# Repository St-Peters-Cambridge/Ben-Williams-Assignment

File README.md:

NSN: 144724831
Name: Ben Williams
Project: Ground control station for model rockets

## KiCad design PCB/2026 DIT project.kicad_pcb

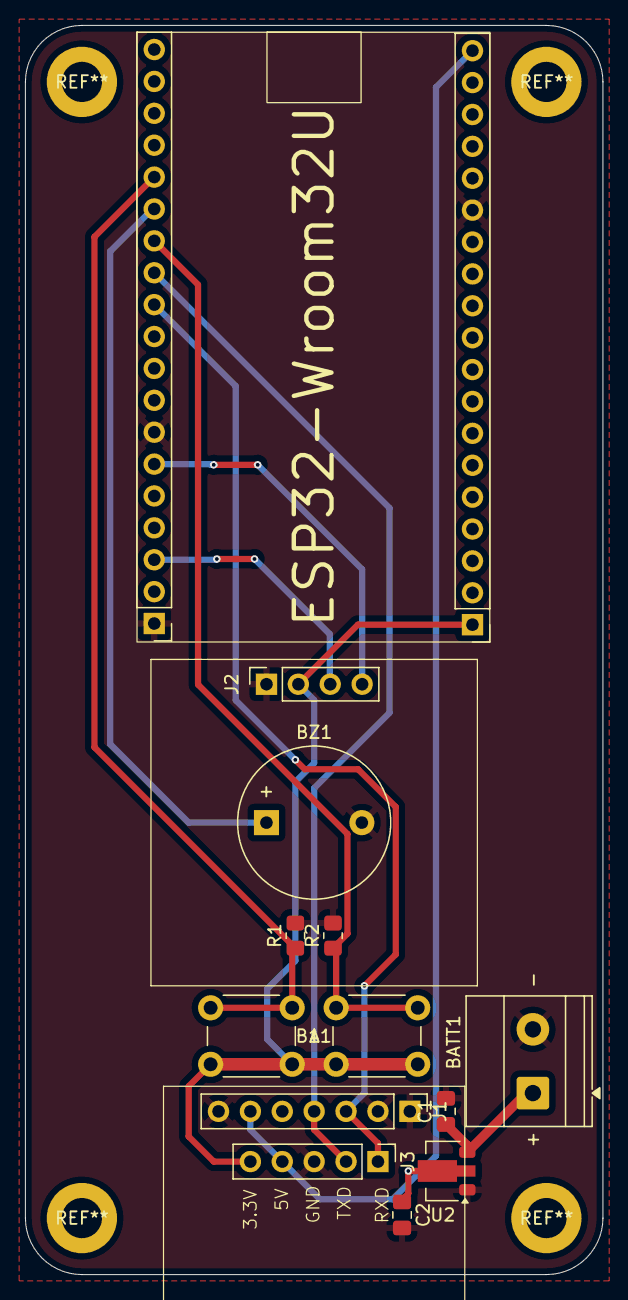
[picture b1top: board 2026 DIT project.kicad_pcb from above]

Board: 2 copper layers, 46.0 x 99.5 mm, 13 parts (0 on the bottom side), 11 nets.

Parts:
A1: SW_Push_Open_Dual; SW_PUSH_6mm
B1: SW_Push_Open_Dual; SW_PUSH_6mm
BATT1: Screw_Terminal_01x02; TerminalBlock_Phoenix_MKDS-1,5-2-5.08_1x02_P5.08mm_Horizont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
BZ1: Buzzer; Buzzer_12x9.5RM7.6
C1: 10u; C_0805_2012Metric_Pad1.18x1.45mm_HandSolder
C2: 22u; C_0805_2012Metric_Pad1.18x1.45mm_HandSolder
J1: Conn_01x07_Socket; PinHeader_1x07_P2.54mm_Vertical
J2: Conn_01x04_Socket; PinSocket_1x04_P2.54mm_Vertical
J3: Conn_01x05_Pin; PinHeader_1x05_P2.54mm_Vertical
R1, R2: 10k; R_0805_2012Metric_Pad1.20x1.40mm_HandSolder
U1: ESP32-WROOM32U; Board
U2: AMS1117-5.0; SOT-89-3

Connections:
+3V3: A1.1, B1.1, J2.2, J3.5, U1.3V3
+5V: C2.1, J1.6, J3.4, U1.5V, U2.2 (VO)
/BTN_A: A1.2, R1.1, U1.2
/BTN_B: B1.2, R2.1, U1.4
/Buzzer: BZ1.1 (+), U1.0
/RXD: J1.3, J3.1, U1.17
/SCL: J2.3, U1.22
/SDA: J2.4, U1.21
/TXD: J1.4, J3.2, U1.16
GND: BATT1.2, BZ1.2 (-), C1.2, C2.2, J1.1, J1.2, J1.7, J2.1, J3.3, R1.2, R2.2, U1.GND, U2.1 (GND)
VCC: BATT1.1, C1.1, U2.3 (VI)

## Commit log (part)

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2026-03-30 Basic setup of app
    Adding all files and basic setup
2026-03-30 Added all menus for PC
2026-03-30 Fixed Linking
2026-03-30 Add README
2026-03-30 Fixing for Pages
2026-03-30 Remove Folder
2026-03-31 Adding Circuit designs
2026-04-21 Work on home page
    Work for 21/04/2026 period 5
2026-04-22 Finished Home Screen
2026-04-22 Fully Fixed Home Menu
2026-04-24 PCB Design
2026-04-24 PCB Design progress
2026-05-03 PCB design process
2026-05-04 PCB design complete
2026-05-07 Making Nav Menu
2026-05-07 Finished Nav Menu
2026-05-07 Adding the nav menu to all other pages
2026-05-11 Making Settings Menu
2026-05-11 Settings Page complete
2026-05-11 Fixed JS Linking
2026-05-13 Settings and Most of Flight Page Complete
2026-05-13 Finished Flight Menu
2026-05-15 Finished PCB Assembly
2026-05-18 Added Receiver Code
2026-05-22 Receiver code updated
2026-05-25 Finished Post Flight Page
2026-05-27 Finished all data views
2026-06-01 Working on Bluetooth / Serial Connections
2026-06-02 Serial Connection
2026-06-03 testing BLE
2026-06-04 Connection to BLE devices
2026-06-07 Work on the Receiver
2026-06-12 Receiver design complete
2026-06-15 Added a method to allow communication in between rocket and ground station
2026-06-18 Successful connection in between transmitter and receiver
2026-06-24 Working on the Receiver Code
2026-06-25 Trying to fix BLE changing on page change
